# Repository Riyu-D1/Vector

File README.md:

# SOMA — a 6-DOF printed robot arm with printed cycloidal actuators

SOMA is a desk-scale robotic arm (6 joints + parallel-jaw gripper) designed
to be driven by software — a script or an agent — over a documented serial
protocol and Python API. The structure is 3D-printed PETG-CF, and the two
heavily loaded joints (shoulder J2, elbow J3) run on **printed 40:1 cycloidal
reducers** driven by brushless motors — the parts that normally force a
desktop arm onto expensive metal gearboxes. Everything in the repo is
parametric: the mechanical CAD is build123d Python, the carrier PCB is
generated by a Python script into a KiCad project, and the verification
reports are generated by the analysis code in `fullcheck/`.

The design is laid out at ~0.48× scale on Seeed's reBot-DevArm joint plan
(CERN-OHL-W-2.0 — see `NOTICE.md` files), re-engineered around commodity
Feetech bus servos and the printed actuators.

*(Render shows the previous wrist revision; the current R9 wrist is below.)*

## What it does

- **Moves**: 6 joints + gripper, ~0.36 m max level-tool reach, ~1.1 kg
  modelled arm mass on a 140×200 mm desk-mount base.
- **Rated payload 0.25 kg** — verified on paper to a safety factor of 2 in
  every pose, including rolled/edge cases, by per-part FEA (minimum
  converged binding margin SF 3.22; see Verification below). Headroom is
  ~0.35 kg peak — it is honestly a 0.25 kg machine, not a 0.5 kg one.
- **Printed cycloidal actuators**: J2/J3 use 40:1 cycloidal modules —
  PETG-CF discs and housings rolling on hardened ISO 8734 steel dowel pins
  (41× Ø3×10 ring pins + 6× Ø3×12 output pins + 3× Ø4×8 locating pins per
  module), Tarot TL2955 4008 330KV motors, ST B-G431B-ESC1 drivers running
  SimpleFOC, AS5600 magnetic encoders, CAN bus at 1 Mbps. Every printed part
  fits a Bambu A1's 256³ bed.
- **Hard torque + safety limits**: joint torque caps are clamped in the ESCs
  themselves (J2 3.0 N·m, J3 2.0 N·m) and in the trajectory planner; a
  switched motor rail (`MOTOR_EN` relay) means motors get no power until the
  host explicitly arms, and a hardware NC e-stop loop drops the rail
  regardless of firmware state.
- **Agent/script interface**: a framed serial host protocol
  (`docs/host-protocol.md`) plus a pure-Python control package
  (`software/robot-os`) with FK/IK, a torque-gated planner, a gravity/payload
  model and a protocol-level simulator — runnable with no hardware attached.

## Actuator map

| Joint | Function | Actuator | Bus |
|---|---|---|---|
| J1 | base yaw | Feetech STS3250 (50 kg·cm stall, 12 V TTL) | Feetech bus A, 1 Mbaud |
| J2 | shoulder | Tarot 4008 + 40:1 printed cycloidal, B-G431B-ESC1 | CAN 1 Mbps, node 2 |
| J3 | elbow | Tarot 4008 + 40:1 printed cycloidal, B-G431B-ESC1 | CAN 1 Mbps, node 3 |
| J4 | wrist pitch | Feetech STS3250 (printed cradle + U-yoke second bearing) | Feetech bus A |
| J5 | wrist yaw | Feetech STS3215 (30 kg·cm class) | Feetech bus A |
| J6 | tool roll | Feetech STS3215 | Feetech bus A |
| Grip | parallel jaw | Feetech STS3215, rack-and-pinion (steel m1 16T pinion + printed racks), 25 mm stroke | Feetech bus A |

J2 and J3 also carry coaxial one-way torsion balance springs
(Springmasters 471671) that unload the motors in forward poses.

## Current specs

| | |
|---|---|
| Axes | 6 joints + parallel-jaw gripper |
| Rated payload | **0.25 kg** — SF ≥ 2 in every pose (see [FULLCHECK.md](FULLCHECK.md)); ~0.35 kg peak headroom |
| Reach | ~0.36 m max (level tool); home TCP at (233.8, 0, 199.2) mm |
| Arm mass | ~1.116 kg modelled (wrist + gripper 0.240 kg) |
| Joint limits | J1 ±150° (printed hard stop ±152.5°), J2 −120…+70°, J3 −180…+30°, J4 ±70°, J5 ±70°, J6 ±180° (auto-sublimited to ±110° when J5 < 0) |
| J2/J3 torque | capped 3.0 / 2.0 N·m in firmware (worst static demand at 0.25 kg: 2.48 / 1.26 N·m); cyclo structural bound ~3.65 N·m |
| Servos | 2× Feetech STS3250 (J1, J4) + 3× STS3215 (J5, J6, gripper), one shared 12 V TTL bus |
| Cycloidal module | 40:1, dual 4.25 mm PETG-CF discs, Ø44.7 mm; ~57×57×54 mm housing; ISO 8734 steel dowels; AS5600 on motor shaft (hard-stop homing each boot) |
| Controller | ESP32-S3-DevKitC-1 on a custom 2-layer carrier PCB (`soma-carrier-v13`) |
| Motor drivers | 2× ST B-G431B-ESC1 (SimpleFOC, CANopen-style protocol) |
| Power | 12 V / 8.5 A Mean Well RS-100-12 mains PSU; 6 A fuse; reverse-polarity protection; switched motor rail via relay K1 |
| Structure | FDM PETG-CF, every part ≤ 200 mm on a Bambu A1 (256³) bed; full print list ≈1.2 L solid — one 1 kg spool covers it |
| Est. build cost | **£674** verified+priced lines / **£825** all-in incl. unverified estimates (GBP, UK suppliers, Nov 2026 — [BOM](final/BOM_FINAL.md)) |
| Status | **Design verified on paper — not yet built.** Whole-arm check verdict: READY TO ORDER at 0.25 kg |

## The base carrier PCB (`soma-carrier-v13`)

One custom board in the base replaces the usual servo-hub + wire ratsnest:

- **ESP32-S3-DevKitC-1 drops into pin sockets** — it is the only MCU in the
  base; everything on the board is hand-solderable (all through-hole except
  one SOIC-8).
- **Power**: 12 V input (XT60 or screw terminal) → reverse-polarity P-FET
  → 6 A fuse → +12 V rail for the five bus servos (KK-254 keyed
  connectors); optional Mini-360 buck for the 5 V logic rail with a
  Schottky USB/board OR-ing so the devkit can stay plugged in.
- **Switched motor rail**: `MOTOR_EN` (IO40) → 2N2222A → Songle SRD-12V
  relay K1 → `+12V_MOT` on two Phoenix outputs feeding the J2/J3 ESCs. The
  relay coil runs through a **J19 NC e-stop loop** — a twist-release
  mushroom cuts the motor rail in hardware, independent of firmware.
- **CAN onboard**: TJA1051T/3 transceiver + CAN header to the two
  B-G431B-ESC1 joint drivers (1 Mbps; far-end termination on the last ESC).
- **Peripherals on board**: SSD1306 OLED socket, MPU6050 IMU socket, EC11
  jog-dial port, WS2812 port, buzzer, IR receiver, DS18B20 temp sensor,
  12 V rail voltage-sense divider, status/power LEDs, test pads.
- **135×115 mm, 2 layers** (F.Cu + B.Cu ground pours), generated
  parametrically by `gen_pcb.py` (parts placed by coordinate, nets routed
  by a grid A\* router) and opened in KiCad 10.

**Fabrication files**: [`order/pcb13_fix/`](order/pcb13_fix/) holds the
orderable v1.3 board (`soma-carrier-v13.kicad_pcb` — a fixed copy; the v1.3
relay pad map was corrected after a datasheet cross-check) and its
[`gerbers/`](order/pcb13_fix/gerbers/) (2-layer, 1.6 mm, HASL lead-free,
1 oz — see [`order/PCB_ORDER.md`](order/PCB_ORDER.md)). Latest DRC: **0
electrical violations, 0 unconnected** (27 benign silkscreen/library
cosmetic notes only). The `pcb/` folder is the older v1.1 board — kept for
history, do not order from it.

*(Image is the earlier v1.1 board; v1.3 adds the K1 motor-rail relay,
reverse-polarity FET and TJA1051 CAN transceiver on the same outline.
Orderable gerbers: `order/pcb13_fix/gerbers/`.)*

## Electronics & firmware

- `firmware/base-node/` — ESP32-S3 (PlatformIO): CAN master, Feetech STS
  bus master, framed host link (115200 8N1), and the pure-C `motor_en`
  safety state machine (two-phase arm: explicit host `ARM_MOTOR`, then
  every ESC must heartbeat inside a 1500 ms boot window; estop / watchdog /
  bus-off / lost heartbeat drops the rail instantly and needs an explicit
  re-arm). Builds clean.
- `firmware/joint-driver/` — one B-G431B-ESC1 per cycloidal joint
  (SimpleFOC; encoder-offset calibration persisted, hard-stop homing each
  boot, phase-current clamps 3.71 A / 2.47 A, 75 ms soft-stop ramp,
  torque caps hard-clamped in EEPROM). Builds clean.
- `firmware/shared/` — pure-C CAN / Feetech / host-link codecs; the Python
  test suite drives the real compiled code via ctypes for byte-exact
  cross-checks.
- `software/robot-os/` — pure-Python `soma_arm` package (numpy only):
  exact FK + limit-checked analytic IK (x, y, z, pitch, roll), min-jerk
  synchronized planner with per-waypoint torque gating, gravity/payload
  model, CLI, and a protocol-level simulator. **84/84 tests pass** on this
  branch. Protocols: [`docs/host-protocol.md`](docs/host-protocol.md),
  [`docs/can-protocol.md`](docs/can-protocol.md); first power-up:
  [`docs/bringup.md`](docs/bringup.md).

## Verification status

The arm has not been built — but it has been checked end-to-end in
analysis. [`FULLCHECK.md`](FULLCHECK.md) (this branch) ran the whole-arm
audit on the current R9 part set:

- **Integration / interference**: 73-part posed assembly, zero undeclared
  intersections at home; per-joint sweeps at 2.5° pass with documented
  exceptions only (the symmetric printed yaw stop at ±152.5°, unreachable
  below-table poses, mm³-class extreme-fold grazes).
- **Mass & torque**: 29,653-pose sweep at 0.25 kg — worst joint at 83% of
  its firmware cap (J2 2.481 N·m); workspace payload bound 0.385 kg.
- **Strength**: converged per-part bolted/pinned CalculiX FEA on every
  load-bearing printed part — all pass all four PETG-CF allowables with
  margin at 0.25 kg; minimum converged binding **SF 3.22** (`dogleg_r`
  compression). The R9 wrist is proven SF ≥ 2 including rolled poses; one
  disclosed borderline remains (w_link5 lip SF 1.96 vs the most
  conservative 6.1 MPa shear bound). 0.38 kg / 0.5 kg ratings are **not**
  met and are disclosed as such.
- **Printability**: all parts ≤ 200 mm, watertight, documented
  orientations/supports; total ≈ 1.2 L PETG-CF.
- **Electronics**: firmware limits match swept mechanical ranges (J1
  clipped to ±150°, 2.5° clear of the printed stop); carrier DRC clean;
  K1 relay pad-map bug found in review and fixed in `order/pcb13_fix/`.
- **BOM**: every bought line has a UK source and price; one Ø3×18 wrist
  dowel is priced TBC.

Mandatory build-stage actions are documented (calibration-coupon print
first, selective pin fit + 200-rev run-in per cyclo module, J4-cradle
heat-set inserts, firm-fit output dowels) — see
[`final/PRINT_LIST.md`](final/PRINT_LIST.md) and
[`final/BUILD_GUIDE.md`](final/BUILD_GUIDE.md).

## Renders

| Whole arm (front) | R9 wrist assembly | Wrist FEA (CalculiX) |
|---|---|---|
|  |  |  |

More: [`final/renders/`](final/renders/) (front/side/wrist close-up),
[`refine/renders/`](refine/renders/) (wrist part sheets). Full assembly:
`final/out/assembly.stl` / `assembly.step.gz`.

## Repo layout

```
├── FULLCHECK.md          # whole-arm verification report + verdict (start here)
├── ARM_HYBRID_V3.md      # design brief (superseded in details — FULLCHECK is current)
├── final/                # ship pack: BOM_FINAL*, PRINT_LIST, BUILD_GUIDE,
│                         #   assembly export (assembly.stl / .step.gz), renders
├── order/                # order pack: UK BOM CSV, PCB_ORDER, STRESS_SANITY,
│   └── pcb13_fix/        #   soma-carrier-v13 KiCad project + gerbers/  ← fab files
├── firmware/             # base-node (ESP32-S3), joint-driver (B-G431B-ESC1),
│                         #   shared pure-C codecs
├── software/robot-os/    # soma_arm Python package: FK/IK, planner, gravity
│                         #   model, CLI, simulator, pytest suite
├── docs/                 # host/CAN protocols, bring-up checklist,
│                         #   firmware-verification, stage status reports
├── fullcheck/            # the verification code itself (collision, torque,
│                         #   probe, per-part FEA pipeline)
├── cad/ cad3/ cyclo4/    # parametric build123d sources + checked STLs:
│   refine/ wrist2/       #   arm2b main structure, D2 overrides, cyclo modules,
│   toolchg/ cradlefix/   #   R9 wrist, tool-changer option, stage archives
│   lighten/ verify/      #
└── upgrade1/ final2/     # earlier stage reports (gravity model, F2 merge)
```

## Licence & attribution

- Overall licence: **TBC** — no top-level LICENSE file yet.
- Joint layout and wrist/gripper/link geometry derive from **Seeed
  reBot-DevArm** under **CERN-OHL-W-2.0** — see `NOTICE.md` in `cad/arm2/`,
  `cad/arm2b/` and `cyclo4/`; modified files stay under the same licence.
- Cycloidal concept credit: Dongil Choi (hackaday.io/project/167688).
- Joint-driver firmware follows the protocol shape of the MIT-licensed
  Berkeley Recoil-Motor-Controller-BESC.

## Status

Design complete and verified on paper (`READY TO ORDER at 0.25 kg` —
[FULLCHECK.md](FULLCHECK.md)). Nothing fabricated or purchased yet: the
next step is printing the parts, fabricating the carrier PCB, and running
the staged bring-up in [`docs/bringup.md`](docs/bringup.md).

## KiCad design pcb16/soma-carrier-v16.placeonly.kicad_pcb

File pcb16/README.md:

# SOMA Base Carrier v1.6

2-layer, all-through-hole carrier board for the base electronics.
Black solder mask + white silkscreen (JLCPCB "black" colour option),
with vector board art (CAPTCHA checkbox + sad-page icon) on F.SilkS.
Replaces the off-the-shelf servo bus hub + the ratsnest of Dupont wires: the
ESP32-S3-DevKitC-1 drops into pin sockets, every servo gets a keyed KK-254
connector, power is fused + distributed on-board, and the useful little
peripherals (display, IMU, jog dial, buzzer, IR, temp, voltage sense,
CAN transceiver, NeoPixel port) are soldered or socketed directly on the board.

Board: 135 x 115 mm, 2 layers (F.Cu + B.Cu GND pours both sides + stitching
vias), all THT — hand-solderable with an iron, no stencil, no SMD (U2 CAN
transceiver is the one SOIC-8 exception). Everything that plugs in uses
standard 2.54 mm pin sockets, so modules stay removable.

v1.5 fixes the CHECK-pcb14 audit findings: the ESP32 socket was mirrored
180° (F1 — power shorts + wrong GPIO), the NeoPixel port lacked a 5 V
level shifter (F2), the 12 V rails were undersized for 10 A (F3), the
servo-bus RX had no clamp footprint (F4), the fuse was documented as
6 A (F5), and J13's pin order didn't match a stock KY-040 (F6).

v1.6 is cosmetic + documentation: black solder mask / white silkscreen,
vector board art, a proper title block, all v1.5 silk DRC violations
resolved, and the docs/BOM corrected (servo bus is the Feetech
half-duplex TTL bus — not RS-485/UART; CAN chip is TJA1051T/3; D7 is
a real placed footprint; BOM lists every part with voltage ratings).

## Power flow

```
12V brick -> J16 XT60 plug  ==OR==  J1 screw terminal
          -> JP1 shunt (power switch; or wire a panel rocker here)
          -> D4 15 V TVS -> F1 (10 A mini blade fuse) -> +12V rail
          -> J4/J5 (STS3215 bus A x2), J3 (buck in), K1 relay (motor feed)
J3 Mini-360 buck (optional) -> +5V rail  ==OR==  J2 external 5V terminal
+5V -> D1 (1N5820 Schottky) -> +5V_MCU -> U1B.21 (ESP32 5V pin)
```

**Use ONE 5 V source only** — fit either the Mini-360 buck on J3 *or* feed
external 5 V into J2, never both. (Silkscreen reminder is on the board.)

The Schottky means USB programming and board power can both be connected
at once — the diode drops board 5 V to ~4.8 V at the 5 V pin so neither
supply fights the other. **D1 orientation: cathode band toward pin 1**
(the +5V_MCU side). D4 is **P6KE15A, unidirectional** — band toward
pin 1 (+12V_IN). A bidirectional P6KE15CA also works and is non-polar.

**F1 is a 10 A mini blade fuse** (v1.4 doc said 6 A — wrong). The +12V
motor feed passes through K1 (SRD-12V, contacts rated 10 A) so firmware
can cut motor power on estop/fault; the servo rails are unfused past F1
by design — the fuse is the only overcurrent device on the 12 V path.

## Connectors

| Ref | What | Pins |
|---|---|---|
| J16 | 12 V input — XT60-M vertical plug | 1=GND, 2=+12V_IN |
| J1 | 12 V input — screw terminal (parallel w/ J16) | 1=+12V_IN, 2=GND |
| JP1 | power-enable shunt (or panel switch) | 1=+12V_IN, 2=+12V_SW |
| J2 | ext 5 V input (skip if Mini-360 fitted) | 1=+5V, 2=GND |
| J3 | Mini-360 buck module (optional) | 1=+12V, 2=GND, 3=+5V, 4=GND |
| J4, J5 | servo bus A (STS3215; Feetech half-duplex TTL bus) | 1=GND, 2=+12V, 3=BUSA_DATA |
| U1A/U1B | ESP32-S3-DevKitC-1 socket (2x 1x22 pin sockets) | USB faces LEFT |
| J9 | emergency stop button | 1=ESTOP, 2=GND |
| J11 | SSD1306 OLED socket (I2C-1) | 1=GND, 2=+3V3, 3=SCL1, 4=SDA1 |
| J12 | GY-521/MPU6050 IMU socket (I2C-1) | 1=+5V, 2=GND, 3=SCL1, 4=SDA1, 7=GND |
| J13 | jog dial port — **direct KY-040 fit** | 1=GND, 2=+3V3, 3=SW, 4=DT, 5=CLK |
| J14 | WS2812 / NeoPixel port | 1=GND, 2=NEO5V(data, shifted), 3=+5V |
| J15 | spare header | 1=+5V, 2=GND, 3/4=NC, 5=+3V3 |
| J17 | CAN bus | 1=GND, 2=CANH, 3=CANL |
| J18, J20 | 12 V motor feed (K1-switched) | 1=+12V_MOT, 2=GND |
| J19 | estop loop NC jumper | 1=RLY_LOW, 2=RLY_SW |
| JP2 | CAN termination jumper | 1=CAN_TERM, 2=CANL |

J13 was re-pinned in v1.5 so a stock KY-040 encoder module plugs straight
on: GND, 3V3, SW, DT(=ENC_B), CLK(=ENC_A). No adapter needed.

## On-board parts (solder-in)

| Ref | Part | Purpose |
|---|---|---|
| D4 | 15 V TVS (DO-201) | input transient clamp |
| F1 | **10 A** mini blade fuse | rail protection |
| C1 | 1000 µF | 12 V bulk |
| C3 | 220 µF | 5 V bulk |
| C2, C4 | 100 nF | decoupling (12 V / 5 V) |
| D1 | 1N5820 Schottky | USB/board 5 V OR-ing |
| R1 | 1k | servo-bus RX coupling (kept) |
| D6 | 3V6 zener (footprint only, optional) | RXA clamp — see F4 note |
| R7, R8 | 30k + 6.8k | 12 V divider -> VSNS ADC (≈0.185 x Vin) |
| U3 | **74AHCT125** (DIP-14 socket) | NEO 3V3 -> 5V level shifter |
| R13 | **330R** | NeoPixel DIN series resistor |
| C7 | **470–1000 µF** | strip supply bulk at J14 |
| C8 | 100 nF | U3 decoupling |
| BZ1 | 5 V active buzzer | fault/estop beeps |
| D7 | 1N4148 | buzzer flyback (inductive load) |
| Q1 | PN2222A TO-92 E-B-C (leads spread to 0.1") | buzzer low-side switch |
| R5 | 1k | buzzer base resistor |
| IR1 | VS1838B IR receiver | IR remote estop/home |
| DSG/DST/DSV | DS18B20 temp sensor (legs on THT pads) | board ambient/overtemp |
| R6 | 4.7k | DS18B20 pull-up |
| D2 + R3 | LED + 330R | power LED |
| D3 + R4 | LED + 330R | status LED (GPIO) |
| U2 | TJA1051T/3 (SOIC-8) | CAN transceiver |
| C5, C6 | 100 nF | U2 VCC/VIO decoupling |
| R9 | 120R | CAN termination (via JP2 jumper) |
| K1 | SRD-12V (contacts 10 A) | motor-power relay, estop chain |
| D5 | 1N4007 | relay-coil flyback |
| Q3 | PN2222A TO-92 E-B-C | relay driver |
| R11, R12 | 1k + 10k | Q3 base resistors |
| Q2 | IRF4905 | reverse-polarity protection (tab = drain) |
| R10 | 10k | Q2 gate pull-down |
| TP1/TP2 | test pads | GND / +12V |
| H1–H4 | M3 | mounting |

TO-92 parts (Q1, Q3, DS1) solder onto 2.54 mm pads — spread the outer
leads. The true 1.27 mm TO-92 inline pitch can't pass a track to the
middle pin, so the board doesn't use it.

## NeoPixel level shifting (F2)

IO4 drives NEO at 3.3 V logic; WS2812 DIN wants ~0.7xVDD ≈ 3.5 V — marginal.
U3 (74AHCT125, powered from +5V) level-shifts it to a real 5 V swing:
`U1B.4 -> U3.2 (1A) -> U3.3 (1Y) -> R13 330R -> J14.2`. All four /OE
pins are grounded (always enabled; 3 spare drivers). C7 sits at the
strip supply pins — fit 470–1000 µF there per the strip length, and R13
330R in series damps the data edge.

## Bus clamp footprint (F4)

The servo data line (BUSA_DATA) is the **Feetech half-duplex TTL bus**
(shared TX/RX on one wire — not RS-485, not a separate UART pair).
R1 (1k) stays as the RX coupling. D6 is a 3V6 zener footprint on RXA,
**unpopulated by default** — fit it only if bench measurement of the
bus high level exceeds ~3.6 V at the ESP32 pin (long-cable reflections
on the STS3215 bus can overshoot).

## ESP32 pin map used (socket positions, real DevKitC-1 v1.1 pinout)

The DevKitC-1 is a 2x22 module; sockets are 1x22. **Socket position N maps
to module pin N — pin 1 of each row is at the USB (west) end.** (v1.4 had
this backwards — the socket was mirrored; v1.5 fixes it per the official
Espressif user-guide pin layout.)

Top row U1B (module J1 side): 1=+3V3, 2=+3V3, 3=RST/EN, 4=NEO(IO4),
5=IRIN(IO5), 6=TEMP(IO6), 7=BUZ(IO7), 9=LEDGPIO(IO16), 10=BUSA_DATA(IO17),
11=SCL1(IO18), 12=SDA1(IO8), 16=VSNS(IO10-ADC1), 17=RXA(IO11),
21=+5V_MCU, 22=GND.

Bottom row U1A (module J3 side): 1=GND, 4=CAN_RX(IO1), 5=CAN_TX(IO2),
8=MOTOR_EN(IO40), 10=ESTOP(IO38), 16=ENC_SW(IO48), 17=ENC_B(IO47),
18=ENC_A(IO21), 21=GND, 22=GND.

Unconnected by design: strapping pins IO0/IO3/IO45/IO46, USB pins
IO19/IO20, console UART0 IO43/IO44, and flash/PSRAM pins IO26-37 on
N16R8 modules. VSNS uses IO10 (ADC1 only — ADC2 conflicts with Wi-Fi).
**Verify the module's silkscreen pin order on assembly** — Espressif has
revised this board.

## Regenerating

    python3 gen_pcb.py            # placement + board skeleton (~minutes)
    python3 reroute.py            # replaces all copper from routes_v16.py
    python3 fill_zones.py         # bakes the GND pours into the file
    ./fab.sh                      # fill + DRC + gerbers + drill

`gen_pcb.py` is the placement/footprint/pad-net authority;
`routes_v16.py` + `reroute.py` are the routing authority (hand-routed
0/45/90 legs with chamfered corners — no autorouter).
`fill_zones.py` uses KiCad's bundled pcbnew `ZONE_FILLER` when present
(exact engine), else falls back to `pour.py`. In the GUI, `B` re-fills
interactively.

Verify with `check_pads.py` (placement probe), `reroute.py --check`
(route rules), `verify_nets.py`, `audit_pins.py`, and `net_stats.py`.

Gerbers + drill in `gerbers/` — upload the folder (or the packaged
`soma-carrier-v16-jlcpcb.zip`) to JLCPCB/OSH Park as-is.
2 layers, 1.6 mm, HASL lead-free, **black solder mask + white silk**
(select "black" at order time — the mask colour is an order option,
not a Gerber feature). ~$5-10 for 5 boards.

## Safety

- 12 V, 10 A fuse on the input — the board can source real current;
  shorted 12 V tracks will bite. Fuse first, power second.
- The SRD-12V relay switches *motor* power only (10 A contacts); the
  servo bus rails are direct from F1.
- Battery/PSU handling: XT60 polarity is marked; the IRF4905 reverse-
  polarity FET protects the board but not a reversed servo.
- No mains anywhere on this board — 12 V SELV only.

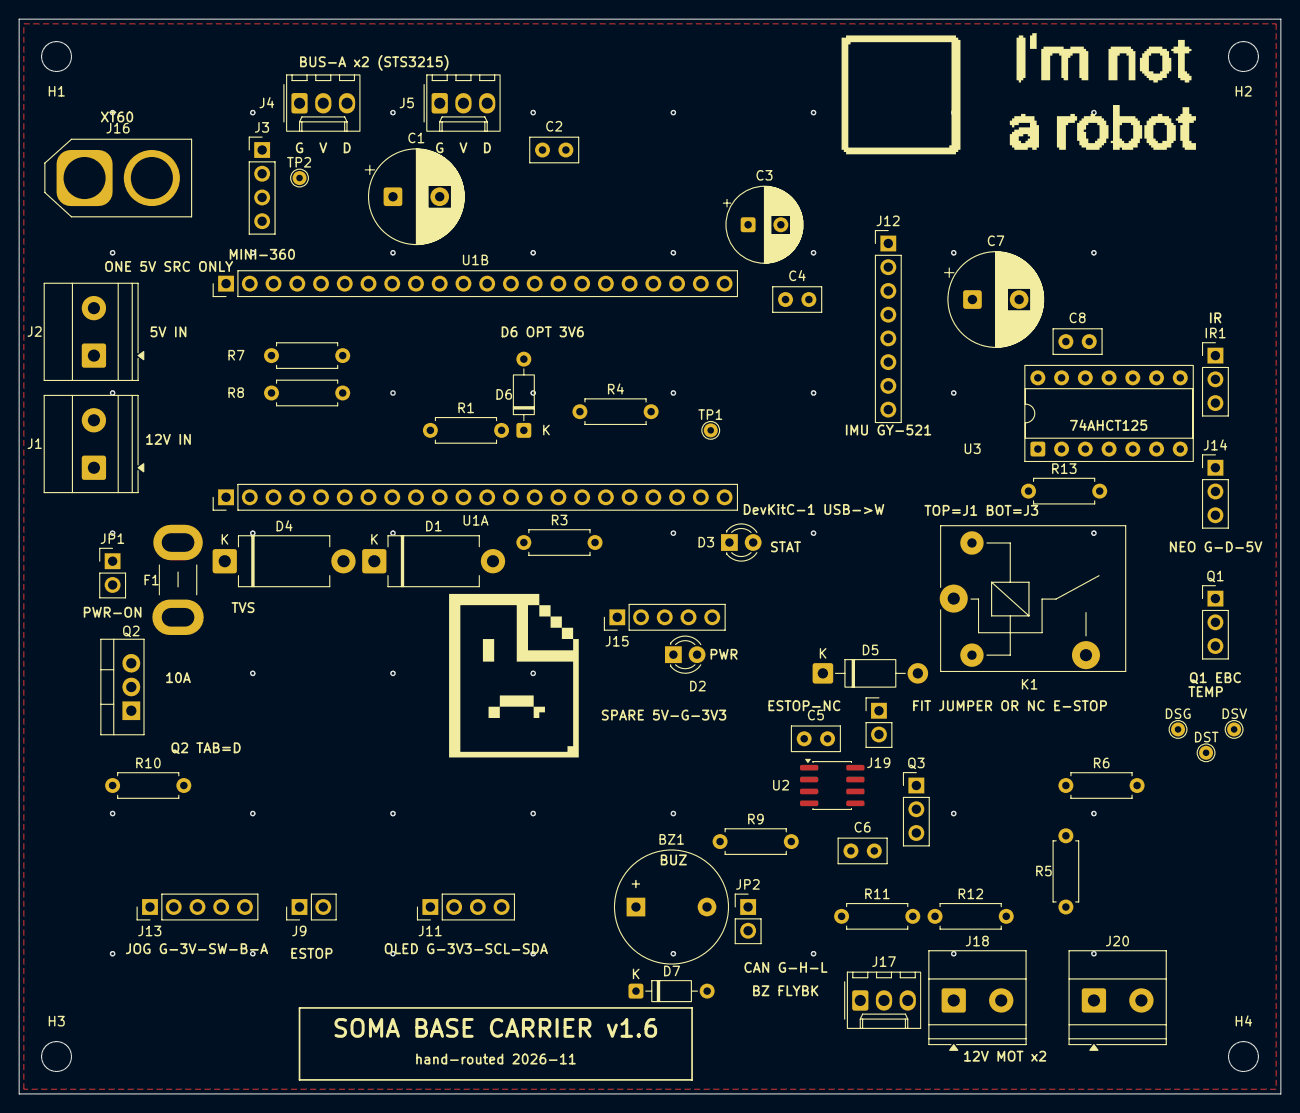
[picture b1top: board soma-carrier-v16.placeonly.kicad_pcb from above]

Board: 2 copper layers, 135.0 x 115.0 mm, 65 parts (0 on the bottom side), 39 nets, no tracks yet.

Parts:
BZ1: BUZZ5V; Buzzer_12x9.5RM7.6
C1: 1000uF; CP_Radial_D10.0mm_P5.00mm
C2, C4, C5, C6, C8: 100nF; C_Disc_D5.0mm_W2.5mm_P2.50mm
C3: 220uF; CP_Radial_D8.0mm_P3.50mm
C7: 470-1000uF; CP_Radial_D10.0mm_P5.00mm
D1: 1N5820; D_DO-201_P12.70mm_Horizontal
D2: PWR; LED_D3.0mm
D3: STAT; LED_D3.0mm
D4: TVS15; D_DO-201_P12.70mm_Horizontal
D5: 1N4007; D_DO-41_SOD81_P10.16mm_Horizontal
D6: 3V6-opt; D_DO-35_SOD27_P7.62mm_Horizontal
D7: 1N4148; D_DO-35_SOD27_P7.62mm_Horizontal
DSG: DS18B20-G; TestPoint_THTPad_D1.5mm_Drill0.7mm
DST: DS18B20-DQ; TestPoint_THTPad_D1.5mm_Drill0.7mm
DSV: DS18B20-V; TestPoint_THTPad_D1.5mm_Drill0.7mm
F1: 10A; Fuse_Blade_Mini_directSolder
H1, H2, H3, H4: M3; MountingHole_3.2mm_M3_DIN965
IR1: VS1838B; PinHeader_1x03_P2.54mm_Vertical
J1: 12V_IN; TerminalBlock_Phoenix_MKDS-1,5-2-5.08_1x02_P5.08mm_Horizont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
J2: 5V_IN; TerminalBlock_Phoenix_MKDS-1,5-2-5.08_1x02_P5.08mm_Horizont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
J3: MINI360; PinHeader_1x04_P2.54mm_Vertical
J4: BUS_A1; Molex_KK-254_AE-6410-03A_1x03_P2.54mm_Vertical
J5: BUS_A2; Molex_KK-254_AE-6410-03A_1x03_P2.54mm_Vertical
J9: ESTOP; PinHeader_1x02_P2.54mm_Vertical
J11: OLED; PinHeader_1x04_P2.54mm_Vertical
J12: IMU; PinHeader_1x08_P2.54mm_Vertical
J13: JOG; PinHeader_1x05_P2.54mm_Vertical
J14: NEOPIX; PinHeader_1x03_P2.54mm_Vertical
J15: SPARE; PinHeader_1x05_P2.54mm_Vertical
J16: XT60; AMASS_XT60-M_1x02_P7.20mm_Vertical
J17: CAN; Molex_KK-254_AE-6410-03A_1x03_P2.54mm_Vertical
J18, J20: 12V_MOT; TerminalBlock_Phoenix_MKDS-1,5-2-5.08_1x02_P5.08mm_Horizont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
J19: ESTOP-NC; PinHeader_1x02_P2.54mm_Vertical
JP1: PWR-ON; PinHeader_1x02_P2.54mm_Vertical
JP2: CAN-TERM; PinHeader_1x02_P2.54mm_Vertical
K1: SRD-12V; Relay_SPST_SANYOU_SRD_Series_Form_A
Q1, Q3: 2N2222A; PinHeader_1x03_P2.54mm_Vertical
Q2: IRF4905; TO-220-3_Vertical
R1, R5, R11: 1k; R_Axial_DIN0207_L6.3mm_D2.5mm_P7.62mm_Horizontal
R3, R4, R13: 330; R_Axial_DIN0207_L6.3mm_D2.5mm_P7.62mm_Horizontal
R6: 4.7k; R_Axial_DIN0207_L6.3mm_D2.5mm_P7.62mm_Horizontal
R7: 30k; R_Axial_DIN0207_L6.3mm_D2.5mm_P7.62mm_Horizontal
R8: 6.8k; R_Axial_DIN0207_L6.3mm_D2.5mm_P7.62mm_Horizontal
R9: 120; R_Axial_DIN0207_L6.3mm_D2.5mm_P7.62mm_Horizontal
R10, R12: 10k; R_Axial_DIN0207_L6.3mm_D2.5mm_P7.62mm_Horizontal
TP1: GND; TestPoint_THTPad_D1.5mm_Drill0.7mm
TP2: +12V; TestPoint_THTPad_D1.5mm_Drill0.7mm
U1A: DevKitC-J3; PinHeader_1x22_P2.54mm_Vertical
U1B: DevKitC-J1; PinHeader_1x22_P2.54mm_Vertical
U2: TJA1051T/3; SOIC-8_3.9x4.9mm_P1.27mm
U3: 74AHCT125; DIP-14_W7.62mm_Socket

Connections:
+3V3: C6.1, DSV.1, IR1.3, J11.2, J13.2, J15.5, R6.1, U1B.1, U1B.2, U2.5
+5V: BZ1.1, C3.1, C4.1, C7.1, C8.1, D1.2, D7.1, J2.1, J3.3, J12.1, J14.3, J15.1, R3.1, U3.14
+5V_MCU: C5.1, D1.1, U1B.21, U2.3
+12V: C1.1, C2.1, D5.1, F1.2, J3.1, J4.2, J5.2, K1.1, K1.3, R7.1, TP2.1
+12V_IN: D4.1, J1.1, J16.2, JP1.1
+12V_MOT: J18.1, J20.1, K1.5
+12V_RP: F1.1, Q2.3
+12V_SW: JP1.2, Q2.2
BUSA_DATA: J4.3, J5.3, R1.1, U1B.10
BUZ: R5.1, U1B.7
BZB: Q1.2, R5.2
BZC: BZ1.2, D7.2, Q1.3
CANH: J17.2, R9.2, U2.7
CANL: J17.3, JP2.2, U2.6
CAN_RX: U1A.4, U2.4
CAN_TERM: JP2.1, R9.1
CAN_TX: U1A.5, U2.1
ENC_A: J13.5, U1A.18
ENC_B: J13.4, U1A.17
ENC_SW: J13.3, U1A.16
ESTOP: J9.1, U1A.10
GND: C1.2, C2.2, C3.2, C4.2, C5.2, C6.2, C7.2, C8.2, D2.1, D3.1, D4.2, D6.2, DSG.1, IR1.2, J1.2, J2.2, J3.2, J3.4, J4.1, J5.1, J9.2, J11.1, J12.2, J12.7, J13.1, J14.1, J15.2, J16.1, J17.1, J18.2, J20.2, Q1.1, Q3.1, R8.1, R10.2, R12.2, TP1.1, U1A.1, U1A.21, U1A.22, U1B.22, U2.2, U2.8, U3.1, U3.4, U3.5, U3.7, U3.9, U3.10, U3.12, U3.13
IRIN: IR1.1, U1B.5
LED1_A: D2.2, R3.2
LED2_A: D3.2, R4.2
LEDGPIO: R4.1, U1B.9
MOTOR_EN: R11.1, U1A.8
NEO: U1B.4, U3.2
NEO5V: J14.2, R13.1
NEO_A: R13.2, U3.3
Q3_B: Q3.2, R11.2, R12.1
RLY_LOW: D5.2, J19.1, K1.2
RLY_SW: J19.2, Q3.3
RP_GATE: Q2.1, R10.1
RXA: D6.1, R1.2, U1B.17
SCL1: J11.3, J12.3, U1B.11
SDA1: J11.4, J12.4, U1B.12
TEMP: DST.1, R6.2, U1B.6
VSNS: R7.2, R8.2, U1B.16

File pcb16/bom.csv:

ref,value,footprint,qty
BZ1,5V active buzzer 12x9.5mm,Buzzer_12x9.5RM7.6,1
C1,1000uF >=25V,CP_Radial_D10.0mm_P5.00mm,1
C2,100nF >=25V (12V rail),C_Disc_D5.0mm_W2.5mm_P2.50mm,1
C3,220uF >=10V,CP_Radial_D8.0mm_P3.50mm,1
C4,100nF >=10V (5V rail),C_Disc_D5.0mm_W2.5mm_P2.50mm,1
C5,100nF >=10V (U2 VCC=5V),C_Disc_D5.0mm_W2.5mm_P2.50mm,1
C6,100nF >=6.3V (U2 VIO=3V3),C_Disc_D5.0mm_W2.5mm_P2.50mm,1
C7,470-1000uF >=10V (5V strip bulk),CP_Radial_D10.0mm_P5.00mm,1
C8,100nF >=10V (U3 on 5V),C_Disc_D5.0mm_W2.5mm_P2.50mm,1
D1,1N5820,D_DO-201_P12.70mm_Horizontal,1
D2,3mm LED (PWR),LED_D3.0mm,1
D3,3mm LED (STAT),LED_D3.0mm,1
D4,P6KE15A 15V unidirectional TVS (band toward pin 1),D_DO-201_P12.70mm_Horizontal,1
D5,1N4007,D_DO-41_SOD81_P10.16mm_Horizontal,1
D6,3V6 zener DO-35 - optional DNP (RXA clamp),D_DO-35_SOD27_P7.62mm_Horizontal,1
D7,1N4148 (buzzer flyback),D_DO-35_SOD27_P7.62mm_Horizontal,1
DSG+DST+DSV,DS18B20 TO-92 (legs on 1.5mm THT pads),TestPoint_THTPad_D1.5mm_Drill0.7mm,3
F1,10A mini blade fuse,Fuse_Blade_Mini_directSolder,1
H1-H4,M3 mounting hole (x4),MountingHole_3.2mm_M3_DIN965,4
IR1,VS1838B IR receiver,PinHeader_1x03_P2.54mm_Vertical,1
J1,12V_IN screw terminal MKDS 5.08,TerminalBlock_Phoenix_MKDS-1 5-2-5.08_1x02_P5.08mm_Horizontal,1
J2,5V_IN screw terminal MKDS 5.08,TerminalBlock_Phoenix_MKDS-1 5-2-5.08_1x02_P5.08mm_Horizontal,1
J3,Mini-360 buck module (pad order 1=+12V 2=GND 3=+5V 4=GND - verify module printing),PinHeader_1x04_P2.54mm_Vertical,1
J4+J5,KK-254 3-pin servo bus A (Feetech half-duplex TTL): 1=GND 2=+12V 3=DATA,Molex_KK-254_AE-6410-03A_1x03_P2.54mm_Vertical,2
J9,ESTOP button header 1x02,PinHeader_1x02_P2.54mm_Vertical,1
J11,SSD1306 OLED socket 1x04 (I2C-1),PinHeader_1x04_P2.54mm_Vertical,1
J12,GY-521/MPU6050 IMU socket 1x08 (I2C-1),PinHeader_1x08_P2.54mm_Vertical,1
J13,KY-040 jog encoder socket 1x05,PinHeader_1x05_P2.54mm_Vertical,1
J14,NeoPixel port 1x03,PinHeader_1x03_P2.54mm_Vertical,1
J15,spare header 1x05,PinHeader_1x05_P2.54mm_Vertical,1
J16,XT60-M vertical plug,AMASS_XT60-M_1x02_P7.20mm_Vertical,1
J17,CAN bus KK-254 1x03 (1=GND 2=CANH 3=CANL),Molex_KK-254_AE-6410-03A_1x03_P2.54mm_Vertical,1
J18+J20,12V_MOT screw terminal MKDS 5.08,TerminalBlock_Phoenix_MKDS-1 5-2-5.08_1x02_P5.08mm_Horizontal,2
J19,estop loop NC jumper 1x02,PinHeader_1x02_P2.54mm_Vertical,1
JP1,power-enable jumper 1x02 + shunt,PinHeader_1x02_P2.54mm_Vertical,1
JP2,CAN termination jumper 1x02 + shunt,PinHeader_1x02_P2.54mm_Vertical,1
K1,SRD-12VDC-SL-A relay (pins 1-2 coil 3=COM 5=NO - verify bottom view),Relay_SPST_SANYOU_SRD_Series_Form_A,1
Q1+Q3,PN2222A TO-92 E-B-C (leads spread onto 2.54mm pads; pin1=E pin2=B pin3=C),PinHeader_1x03_P2.54mm_Vertical,2
Q2,IRF4905 (tab = drain),TO-220-3_Vertical,1
R1,1k (servo-bus RX coupling),R_Axial_DIN0207_L6.3mm_D2.5mm_P7.62mm_Horizontal,1
R3+R4,330R,R_Axial_DIN0207_L6.3mm_D2.5mm_P7.62mm_Horizontal,2
R5+R11,1k,R_Axial_DIN0207_L6.3mm_D2.5mm_P7.62mm_Horizontal,2
R6,4.7k (DS18B20 pull-up),R_Axial_DIN0207_L6.3mm_D2.5mm_P7.62mm_Horizontal,1
R7,30k,R_Axial_DIN0207_L6.3mm_D2.5mm_P7.62mm_Horizontal,1
R8,6.8k,R_Axial_DIN0207_L6.3mm_D2.5mm_P7.62mm_Horizontal,1
R9,120R (CAN termination via JP2),R_Axial_DIN0207_L6.3mm_D2.5mm_P7.62mm_Horizontal,1
R10+R12,10k,R_Axial_DIN0207_L6.3mm_D2.5mm_P7.62mm_Horizontal,2
R13,330R (NeoPixel DIN series),R_Axial_DIN0207_L6.3mm_D2.5mm_P7.62mm_Horizontal,1
TP1,GND test pad,TestPoint_THTPad_D1.5mm_Drill0.7mm,1
TP2,+12V test pad,TestPoint_THTPad_D1.5mm_Drill0.7mm,1
U1A+U1B,ESP32-S3-DevKitC-1 on 2x 1x22 pin sockets (USB faces LEFT),PinHeader_1x22_P2.54mm_Vertical,2
U2,TJA1051T/3 CAN transceiver,SOIC-8_3.9x4.9mm_P1.27mm,1
U3,74AHCT125 DIP-14 + socket (NeoPixel 3V3->5V shifter),DIP-14_W7.62mm_Socket,1

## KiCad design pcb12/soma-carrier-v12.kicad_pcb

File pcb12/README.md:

# SOMA Base Carrier v1.1

2-layer, all-through-hole, **zero ICs** carrier board for the base electronics.
Replaces the off-the-shelf servo bus hub + the ratsnest of Dupont wires: the
ESP32-S3-DevKitC-1 drops into pin sockets, every servo gets a keyed KK-254
connector, power is fused + distributed on-board, and the useful little
peripherals (display, IMU, jog dial, buzzer, IR, temp, voltage sense,
addressable-LED port) are soldered or socketed directly on the board.

Board: 135 x 115 mm, 2 layers (F.Cu + B.Cu GND pours both sides + stitching
vias), all THT — hand-solderable with an iron, no stencil, no SMD. Everything
that plugs in uses standard 2.54 mm pin sockets, so modules stay removable.

Generated parametrically by `gen_pcb.py` (same approach as `cad/`): parts are
placed by coordinate, nets by name, and a grid A* router lays the copper
(3-D search — signals hop layers through vias where the plane is congested).

## Power flow

```
12V brick -> J16 XT60 plug  ==OR==  J1 screw terminal
          -> JP1 shunt (power switch; or wire a panel rocker here)
          -> D4 15 V TVS -> F1 (6 A mini blade fuse) -> +12V rail
          -> J4/J5 (STS3215 bus A x2), J6 (HTD-45H bus B), J3 (buck in)
J3 Mini-360 buck (optional) -> +5V rail  ==OR==  J2 external 5V terminal
+5V -> D1 (1N5820 Schottky) -> +5V_MCU -> U1B.2 (ESP32 5V pin)
```

The Schottky means USB programming and board power can both be connected
at once — the diode drops board 5 V to ~4.8 V at the 5 V pin so neither
supply fights the other. **D1 orientation: cathode band toward pin 1**
(the +5V_MCU side). D4 (TVS) is non-polar if you fit a bidirectional
part (P6KE15CA); band toward pin 1 (+12V_IN) for a unipolar one.

## Connectors

| Ref | What | Pins |
|---|---|---|
| J16 | 12 V input — XT60-M vertical plug | 1=GND, 2=+12V_IN |
| J1 | 12 V input — screw terminal (parallel w/ J16) | 1=+12V_IN, 2=GND |
| JP1 | power-enable shunt (or panel switch) | 1=+12V_IN, 2=+12V_SW |
| J2 | ext 5 V input (skip if Mini-360 fitted) | 1=+5V, 2=GND |
| J3 | Mini-360 buck module (optional) | 1=+12V, 2=GND, 3=+5V, 4=GND |
| J4, J5 | servo bus A (STS3215) | 1=GND, 2=+12V, 3=BUSA_DATA |
| J6 | servo bus B (HTD-45H) | 1=GND, 2=+12V, 3=BUSB_DATA |
| U1A/U1B | ESP32-S3-DevKitC-1 socket (2x 1x22 pin sockets) | USB faces LEFT |
| J7 | SEA encoder J2 (I2C) | 1=SDA1, 2=+3V3, 3=GND, 4=SCL1 |
| J8 | SEA encoder J3 (I2C) | 1=+3V3, 2=GND, 3=SDA2, 4=SCL2 |
| J9 | emergency stop | 1=ESTOP, 2=GND |
| J10 | wrist node | 1=GND, 2=WTX, 3=WRX, 4=+5V |
| J11 | SSD1306 OLED socket (I2C-1) | 1=GND, 2=+3V3, 3=SCL1, 4=SDA1 |
| J12 | GY-521/MPU6050 IMU socket (I2C-1) | 1=+5V, 2=GND, 3=SCL1, 4=SDA1, 7=GND |
| J13 | jog dial port (EC11 encoder) | 1=+3V3, 2=GND, 3=ENC_B, 4=ENC_A, 5=ENC_SW |
| J14 | WS2812 / NeoPixel port | 1=GND, 2=NEO(data), 3=+5V |
| J15 | spare header | 1=+5V, 2=GND, 3=SP1, 4=SP2, 5=+3V3 |

Servo-bus coupling is passive: ESP32 TX drives DATA directly, RX listens
through R1/R2 (1k). Firmware ignores its own echo — the usual trick for
single-wire TTL buses without a transceiver IC.

## On-board parts (solder-in)

| Ref | Part | Purpose |
|---|---|---|
| D4 | 15 V TVS (DO-201) | input transient clamp |
| F1 | 6 A mini blade fuse | rail protection |
| C1 | 1000 µF | 12 V bulk |
| C3 | 220 µF | 5 V bulk |
| C2, C4 | 100 nF | decoupling (12 V / 5 V) |
| D1 | 1N5820 Schottky | USB/board 5 V OR-ing |
| R1, R2 | 1k | servo-bus RX coupling |
| R7, R8 | 30k + 6.8k | 12 V divider -> VSNS ADC (≈0.185 x Vin) |
| BZ1 | 5 V active buzzer | fault/estop beeps |
| Q1 | 2N2222A (leads spread to 0.1") | buzzer low-side switch |
| R5 | 1k | buzzer base resistor |
| IR1 | VS1838B IR receiver | IR remote estop/home |
| DS1 | DS18B20 temp sensor (leads spread) | board ambient/overtemp |
| R6 | 4.7k | DS18B20 pull-up |
| D2 + R3 | LED + 330R | power LED |
| D3 + R4 | LED + 330R | status LED (GPIO) |
| TP1/TP2 | test pads | GND / +12V |
| H1–H4 | M3 | mounting |

TO-92 parts (Q1, DS1) solder onto 2.54 mm pads — spread the outer leads.
The true 1.27 mm TO-92 inline pitch can't pass a track to the middle pin,
so the board doesn't use it.

## ESP32 pin map used (socket positions, real DevKitC-1 v1.1 pinout)

The DevKitC-1 is a 2x22 module; sockets are 1x22. Socket position N maps to
the module pin at that position — pin 1 of each row is at the USB (west) end.

Top row U1B (module J1 side): 1=GND, 2=+5V_MCU, 5=RXB(IO12), 6=RXA(IO11),
7=VSNS(IO10-ADC1), 11=SDA1(IO8), 12=SCL1(IO18), 13=BUSA_DATA(IO17),
14=LEDGPIO(IO16), 15=BUSB_DATA(IO15), 16=BUZ(IO7), 17=TEMP(IO6),
18=IRIN(IO5), 19=NEO(IO4), 21=+3V3, 22=+3V3.

Bottom row U1A (module J3 side): 1=GND, 2=GND, 5=ENC_A(IO21), 6=ENC_B(IO47),
7=ENC_SW(IO48), 13=ESTOP(IO38), 14=WRX(IO39), 15=WTX(IO40), 16=SCL2(IO41),
17=SDA2(IO42), 18=SP1(IO2), 19=SP2(IO1), 22=GND.

Unconnected by design: strapping pins IO0/IO3/IO45/IO46, USB pins
IO19/IO20, console UART0 IO43/IO44, and flash/PSRAM pins IO26-37 on
N16R8 modules. VSNS uses IO10 (ADC1 only — ADC2 conflicts with Wi-Fi).
**Verify the module's silkscreen pin order on assembly** — Espressif has
revised this board.

## Regenerating

    python3 gen_pcb.py            # ~15-25 min: builds + autoroutes the board
    python3 fill_zones.py         # bakes the GND pours into the file
    kicad-cli pcb drc --format json --output drc.json \
        soma-carrier-v12.kicad_pcb

`fill_zones.py` uses KiCad's bundled pcbnew `ZONE_FILLER` when present
(exact engine — needed because headless refill ignores the generator's
K9-style zone sexpr unless the rule-area flag is cleared), else falls
back to `pour.py` (build123d booleans emitting `filled_polygon` data).
In the GUI, `B` re-fills interactively.

Routing notes for future edits: J13 pad3/4 dive north on staggered
columns; pad5 (ENC_SW) dives south via the deep lane reached from the
EAST (x36-38 descent) — the J9 pad+stub marks wall x29-35,y76-83. The
merged R3/R6 keepouts (x48-66,y50-58) force SDA1/SCL1 transit to y46-48
and parallel lanes at y35.8/37.6 under C4/over TP2. WTX uses the far
east x87-88 descent + deep lane; WRX uses the x60 slot + field dive.
J13 pad 1 is +3V3 (fed from the west). Keep dive waypoints ~1.6 mm
below pad centres.

Gerbers + drill in `gerbers/` — upload the folder to JLCPCB/OSH Park as-is.
2 layers, 1.6 mm, HASL, any colour. ~$5-10 for 5 boards.

Last verified DRC: 0 clearance / 0 track / 0 via electrical violations,
0 non-GND unconnected; 2 GND pads (J15.2, TP1.1) sit in pour-starved
pockets — acceptable, or add a stitched via nearby. Remaining report
items are silkscreen cosmetics and generated-library footprint diffs.

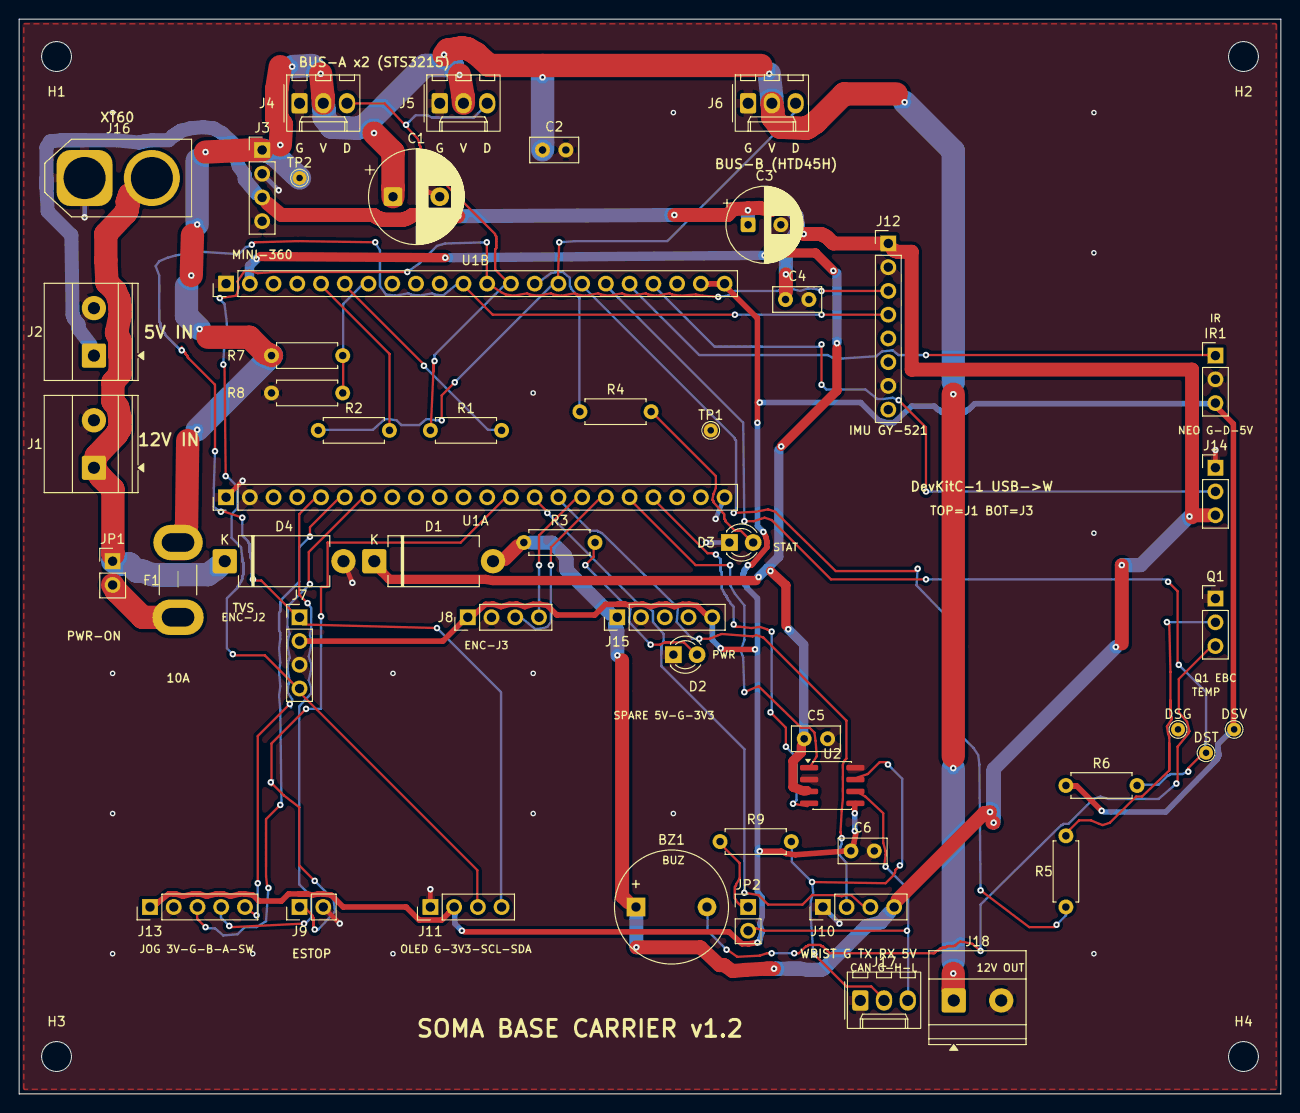
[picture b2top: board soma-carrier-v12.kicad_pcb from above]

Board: 2 copper layers, 135.0 x 115.0 mm, 55 parts (0 on the bottom side), 36 nets.

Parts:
BZ1: BUZZ5V; Buzzer_12x9.5RM7.6
C1: 1000uF; CP_Radial_D10.0mm_P5.00mm
C2, C4, C5, C6: 100nF; C_Disc_D5.0mm_W2.5mm_P2.50mm
C3: 220uF; CP_Radial_D8.0mm_P3.50mm
D1: 1N5820; D_DO-201_P12.70mm_Horizontal
D2: PWR; LED_D3.0mm
D3: STAT; LED_D3.0mm
D4: TVS15; D_DO-201_P12.70mm_Horizontal
DSG: DS18B20-G; TestPoint_THTPad_D1.5mm_Drill0.7mm
DST: DS18B20-DQ; TestPoint_THTPad_D1.5mm_Drill0.7mm
DSV: DS18B20-V; TestPoint_THTPad_D1.5mm_Drill0.7mm
F1: 10A; Fuse_Blade_Mini_directSolder
H1, H2, H3, H4: M3; MountingHole_3.2mm_M3_DIN965
IR1: VS1838B; PinHeader_1x03_P2.54mm_Vertical
J1: 12V_IN; TerminalBlock_Phoenix_MKDS-1,5-2-5.08_1x02_P5.08mm_Horizont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
J2: 5V_IN; TerminalBlock_Phoenix_MKDS-1,5-2-5.08_1x02_P5.08mm_Horizont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
J3: MINI360; PinHeader_1x04_P2.54mm_Vertical
J4: BUS_A1; Molex_KK-254_AE-6410-03A_1x03_P2.54mm_Vertical
J5: BUS_A2; Molex_KK-254_AE-6410-03A_1x03_P2.54mm_Vertical
J6: BUS_B; Molex_KK-254_AE-6410-03A_1x03_P2.54mm_Vertical
J7: ENC_J2; PinHeader_1x04_P2.54mm_Vertical
J8: ENC_J3; PinHeader_1x04_P2.54mm_Vertical
J9: ESTOP; PinHeader_1x02_P2.54mm_Vertical
J10: WRIST; PinHeader_1x04_P2.54mm_Vertical
J11: OLED; PinHeader_1x04_P2.54mm_Vertical
J12: IMU; PinHeader_1x08_P2.54mm_Vertical
J13: JOG; PinHeader_1x05_P2.54mm_Vertical
J14: NEOPIX; PinHeader_1x03_P2.54mm_Vertical
J15: SPARE; PinHeader_1x05_P2.54mm_Vertical
J16: XT60; AMASS_XT60-M_1x02_P7.20mm_Vertical
J17: CAN; Molex_KK-254_AE-6410-03A_1x03_P2.54mm_Vertical
J18: 12V_OUT; TerminalBlock_Phoenix_MKDS-1,5-2-5.08_1x02_P5.08mm_Horizont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
JP1: PWR-ON; PinHeader_1x02_P2.54mm_Vertical
JP2: CAN-TERM; PinHeader_1x02_P2.54mm_Vertical
Q1: 2N2222A; PinHeader_1x03_P2.54mm_Vertical
R1, R2, R5: 1k; R_Axial_DIN0207_L6.3mm_D2.5mm_P7.62mm_Horizontal
R3, R4: 330; R_Axial_DIN0207_L6.3mm_D2.5mm_P7.62mm_Horizontal
R6: 4.7k; R_Axial_DIN0207_L6.3mm_D2.5mm_P7.62mm_Horizontal
R7: 30k; R_Axial_DIN0207_L6.3mm_D2.5mm_P7.62mm_Horizontal
R8: 6.8k; R_Axial_DIN0207_L6.3mm_D2.5mm_P7.62mm_Horizontal
R9: 120; R_Axial_DIN0207_L6.3mm_D2.5mm_P7.62mm_Horizontal
TP1: GND; TestPoint_THTPad_D1.5mm_Drill0.7mm
TP2: +12V; TestPoint_THTPad_D1.5mm_Drill0.7mm
U1A: DevKitC-J3; PinHeader_1x22_P2.54mm_Vertical
U1B: DevKitC-J1; PinHeader_1x22_P2.54mm_Vertical
U2: TJA1051T/3; SOIC-8_3.9x4.9mm_P1.27mm

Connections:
+3V3: C6.1, DSV.1, IR1.3, J7.2, J8.1, J11.2, J13.1, J15.5, R6.1, U1B.21, U1B.22, U2.5
+5V: BZ1.1, C3.1, C4.1, D1.2, J2.1, J3.3, J10.4, J12.1, J14.3, J15.1, R3.1
+5V_MCU: C5.1, D1.1, U1B.2, U2.3
+12V: C1.1, C2.1, F1.2, J3.1, J4.2, J5.2, J6.2, J18.1, R7.1, TP2.1
+12V_IN: D4.1, J1.1, J16.2, JP1.1
+12V_SW: F1.1, JP1.2
BUSA_DATA: J4.3, J5.3, R1.1, U1B.13
BUSB_DATA: J6.3, R2.1, U1B.15
BUZ: R5.1, U1B.16
BZB: Q1.2, R5.2
BZC: BZ1.2, Q1.3
CANH: J17.2, R9.2, U2.7
CANL: J17.3, JP2.2, U2.6
CAN_RX: U1A.19, U2.4
CAN_TERM: JP2.1, R9.1
CAN_TX: U1A.18, U2.1
ENC_A: J13.4, U1A.5
ENC_B: J13.3, U1A.6
ENC_SW: J13.5, U1A.7
ESTOP: J9.1, U1A.13
GND: C1.2, C2.2, C3.2, C4.2, C5.2, C6.2, D2.1, D3.1, D4.2, DSG.1, IR1.2, J1.2, J2.2, J3.2, J3.4, J4.1, J5.1, J6.1, J7.3, J8.2, J9.2, J10.1, J11.1, J12.2, J12.7, J13.2, J14.1, J15.2, J16.1, J17.1, J18.2, Q1.1, R8.1, TP1.1, U1A.1, U1A.2, U1A.22, U1B.1, U2.2, U2.8
IRIN: IR1.1, U1B.18
LED1_A: D2.2, R3.2
LED2_A: D3.2, R4.2
LEDGPIO: R4.1, U1B.14
NEO: J14.2, U1B.19
RXA: R1.2, U1B.6
RXB: R2.2, U1B.5
SCL1: J7.4, J11.3, J12.3, U1B.12
SCL2: J8.4, U1A.16
SDA1: J7.1, J11.4, J12.4, U1B.11
SDA2: J8.3, U1A.17
TEMP: DST.1, R6.2, U1B.17
VSNS: R7.2, R8.2, U1B.7
WRX: J10.3, U1A.14
WTX: J10.2, U1A.15

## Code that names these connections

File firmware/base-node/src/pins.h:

/*
 * pins.h — ESP32-S3 GPIO map for the soma-carrier PCB **v1.3**
 * (~/Vector-wt/pcb13/pcb13/STATUS-pcb13.md is authoritative).
 * Carrier board is FINAL — do not remap.
 *
 * v1.3 changes vs the v1.1-era map: bus B (IO15/12), I2C2 (IO41/42) and
 * the wrist UART (IO39/40) were REMOVED from the board. Net WTX on
 * U1A.15 became MOTOR_EN — it now drives relay K1 (via Q3/R11/R12 and
 * the J19 NC e-stop loop) which switches +12V_MOT on J18/J20.
 *
 *   U1A pad18 IO2  -> SP1 -> J15.3   CAN_TX to TJA1051T/3 transceiver D
 *   U1A pad19 IO1  -> SP2 -> J15.4   CAN_RX from transceiver R
 *   U1A pad13 IO38 -> ESTOP -> J9.1  estop sense (NC loop to GND, J9.2)
 *   U1A pad15 IO40 -> MOTOR_EN -> R11 -> Q3 base  relay K1 low side
 *                    (through the J19 NC e-stop loop; HIGH = motors get
 *                    +12V_MOT, LOW by default)
 *   U1B pad13 IO17 -> BUSA_DATA -> J4/J5  Feetech bus A TX
 *                    (J1 STS3250 id1, J4/J5/J6 STS3215 id4/5/6, grip id7)
 *   U1B pad6  IO11 -> RXA via R1          Feetech bus A RX (1k coupled)
 *   U1B pad14 IO16 -> LEDGPIO via R4      status LED (D3 STAT)
 *   U1B pad16 IO7  -> BUZ via R5/Q1       buzzer
 *   U1B pad7  IO10 -> VSNS ADC1           12 V rail voltage divider
 *   U1B pad11 IO8 -> SDA1, pad12 IO18 -> SCL1  I2C-1 (J11 OLED, J12 IMU)
 *
 * Host link: Serial = UART0 console on the DevKit's USB-UART port
 * (IO43/IO44, not routed through the carrier).
 */
#pragma once

#include <driver/gpio.h>

/* CAN transceiver on spare header J15 (TJA1051T/3 on carrier v1.3) */
#define PIN_CAN_TX    GPIO_NUM_2    /* J15.3 = SP1 */
#define PIN_CAN_RX    GPIO_NUM_1    /* J15.4 = SP2 */

/* safety */
#define PIN_ESTOP     GPIO_NUM_38   /* J9.1; NC loop to GND.
                                     * HIGH (loop open) = ESTOP */
#define PIN_MOTOR_EN  GPIO_NUM_40   /* R11 -> Q3 -> relay K1 coil low
                                     * side through the J19 NC loop.
                                     * HIGH = motors powered (+12V_MOT).
                                     * MUST stay LOW until the safety
                                     * state machine closes it. */

/* Feetech servo bus A: J1 STS3250 (id 1), J4/J5/J6 STS3215 (id 4/5/6),
 * gripper STS3215 (id 7) */
#define PIN_BUSA_TX   GPIO_NUM_17
#define PIN_BUSA_RX   GPIO_NUM_11

/* misc carrier peripherals */
#define PIN_LED_STAT  GPIO_NUM_16
#define PIN_BUZZER    GPIO_NUM_7
#define PIN_VSENSE    GPIO_NUM_10   /* ADC1_CH9 */

/* I2C-1 only (I2C-2 was removed from the board in v1.3) */
#define PIN_SDA1      GPIO_NUM_8
#define PIN_SCL1      GPIO_NUM_18
